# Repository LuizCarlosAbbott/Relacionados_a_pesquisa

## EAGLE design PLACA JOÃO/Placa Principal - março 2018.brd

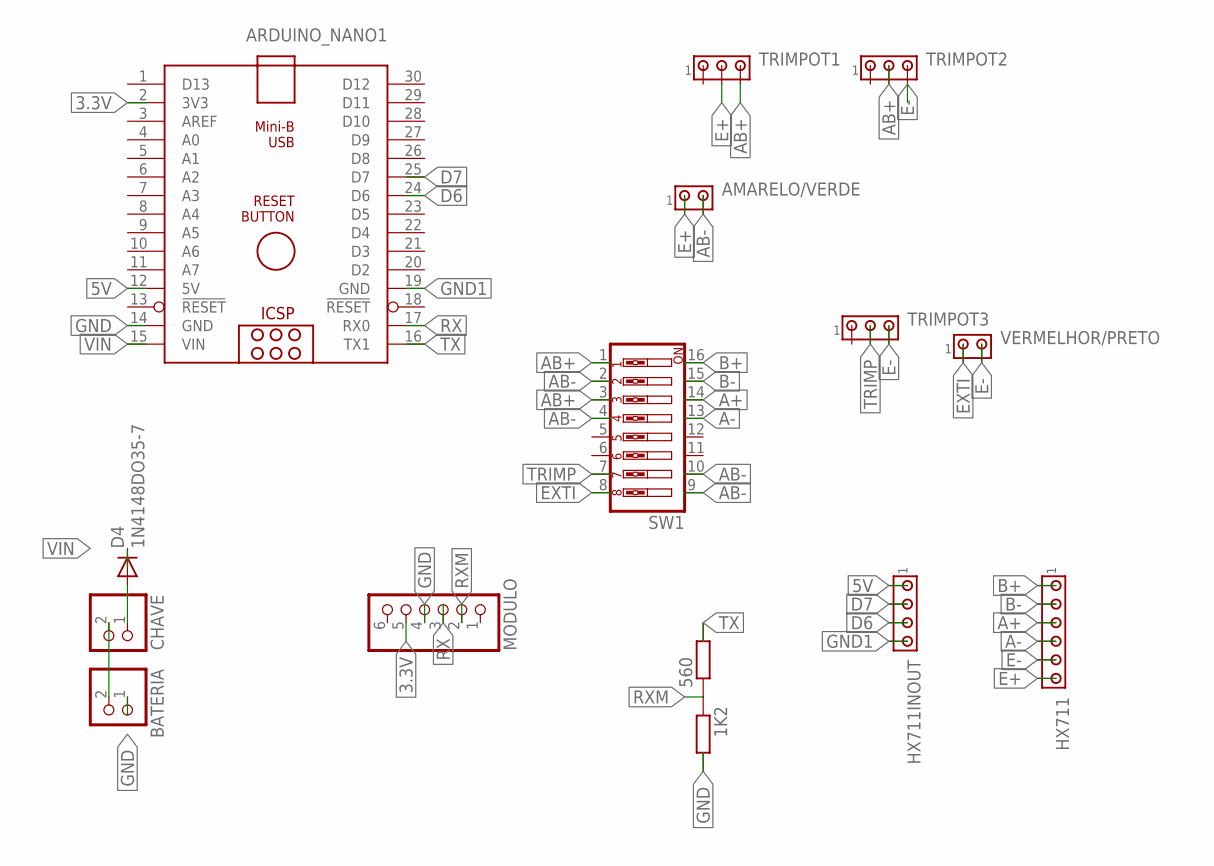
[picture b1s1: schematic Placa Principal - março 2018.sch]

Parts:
1K2, 560: R-EU_0204/5; 0204/5
AMARELO/VERDE: MTA02-100; 10X02MTA
ARDUINO_NANO1: ARDUINO_NANO
BATERIA: PINHD-1X2; 1X02
CHAVE: PINHD-1X2; 1X02
D4: 1N4148DO35-7; DO35-7
HX711: MTA06-100; 10X06MTA
HX711INOUT: MTA04-100; 10X04MTA
MODULO: PINHD-1X6; 1X06
SW1: SW_DIP-8; EDG-08
TRIMPOT1, TRIMPOT2, TRIMPOT3: MTA03-100; 10X03MTA
VERMELHOR/PRETO: MTA02-100; 10X02MTA

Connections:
3.3V: ARDUINO_NANO1.2 (3V3), MODULO.5
5V: ARDUINO_NANO1.12 (5V), HX711INOUT.1
A+: HX711.3, SW1.14
A-: HX711.4, SW1.13
AB+: SW1.1, SW1.3, TRIMPOT1.3, TRIMPOT2.2
AB-: AMARELO/VERDE.2, SW1.2, SW1.4, SW1.9, SW1.10
B+: HX711.1, SW1.16
B-: HX711.2, SW1.15
D6: ARDUINO_NANO1.24 (D6), HX711INOUT.3
D7: ARDUINO_NANO1.25 (D7), HX711INOUT.2
E+: AMARELO/VERDE.1, HX711.6, TRIMPOT1.2
E-: HX711.5, TRIMPOT2.3, TRIMPOT3.3, VERMELHOR/PRETO.2
EXTI: SW1.8, VERMELHOR/PRETO.1
GND: 1K2.2, ARDUINO_NANO1.14 (GND), BATERIA.1, MODULO.4
GND1: ARDUINO_NANO1.19 (GND), HX711INOUT.4
unnamed: BATERIA.2, CHAVE.2
unnamed: CHAVE.1, D4.A
RX: ARDUINO_NANO1.17 (RX0), MODULO.3
RXM: 1K2.1, 560.1, MODULO.2
TRIMP: SW1.7, TRIMPOT3.2
TX: 560.2, ARDUINO_NANO1.16 (TX1)
VIN: ARDUINO_NANO1.15 (VIN), D4.C

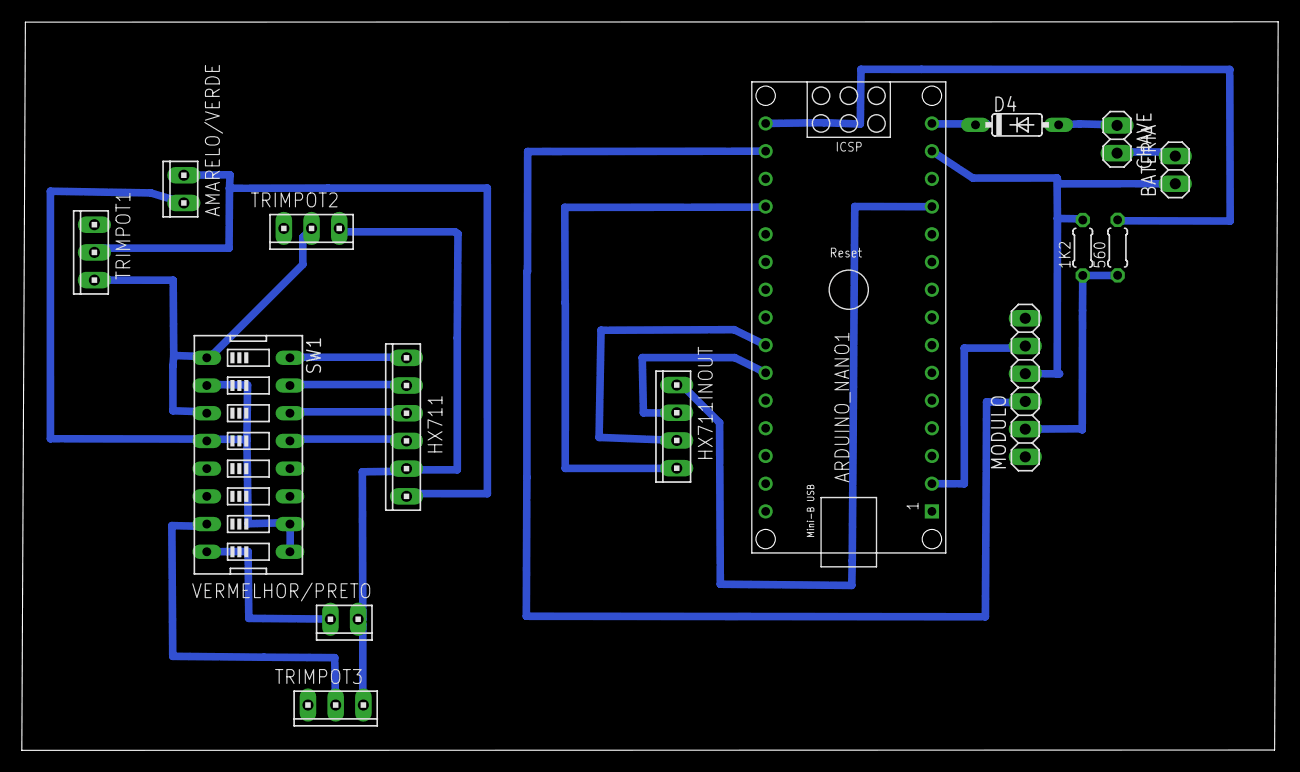
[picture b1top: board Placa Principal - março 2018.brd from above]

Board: 2 copper layers, 115.2 x 66.8 mm, 15 parts (0 on the bottom side), 22 nets.

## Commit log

2018-06-07 Placa ortoleg do joão
